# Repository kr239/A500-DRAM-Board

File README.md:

# A500-DRAM-Board

Replace the old 44256 DRAM chips on your A500+ with newer SOJ-40 EDO memory! No more hunting around trying to find stocks of old 44256 DRAM chips on eBay from dubious sellers with no idea if they work or not - i designed this board to fit 2 x 512KB (4MBit) EDO RAM chips so that you can address 1MB of RAM.

I used IS41C16257-35 chips (256k x 16) as they're cheap, abundant and they have exactly 9 address lines (A0 to A8) so no need for a CPLD to generate the A9 signal that's required for newer chips.

It's a pretty simple design, just three decoupling caps for each DRAM IC and the correct pin layout for it to plug into the A500 board. 

This Rev3 design reduces the component count, the board size and improves the layout and routing considerably.

Project is all done in KiCad 5.1.2

If you've been linked to this project from elsewhere - please note, while I might occasionally have some of these PCB's available, I don't typically have these produced and for sale, except for testing. To purchase one, please go here:

https://www.pcbway.com/project/shareproject/Amiga_500__DRAM_Replacement_Board.html

# Bill of Materials

6 x X7R 0.1uF MLCC SMD Capacitors (1206 (imperial))

2 x IS41C16257-35 5v 256x16 EDO DRAM (SOJ-40)

4 x 10-pin SIL Headers (Harwin M20-9771042)

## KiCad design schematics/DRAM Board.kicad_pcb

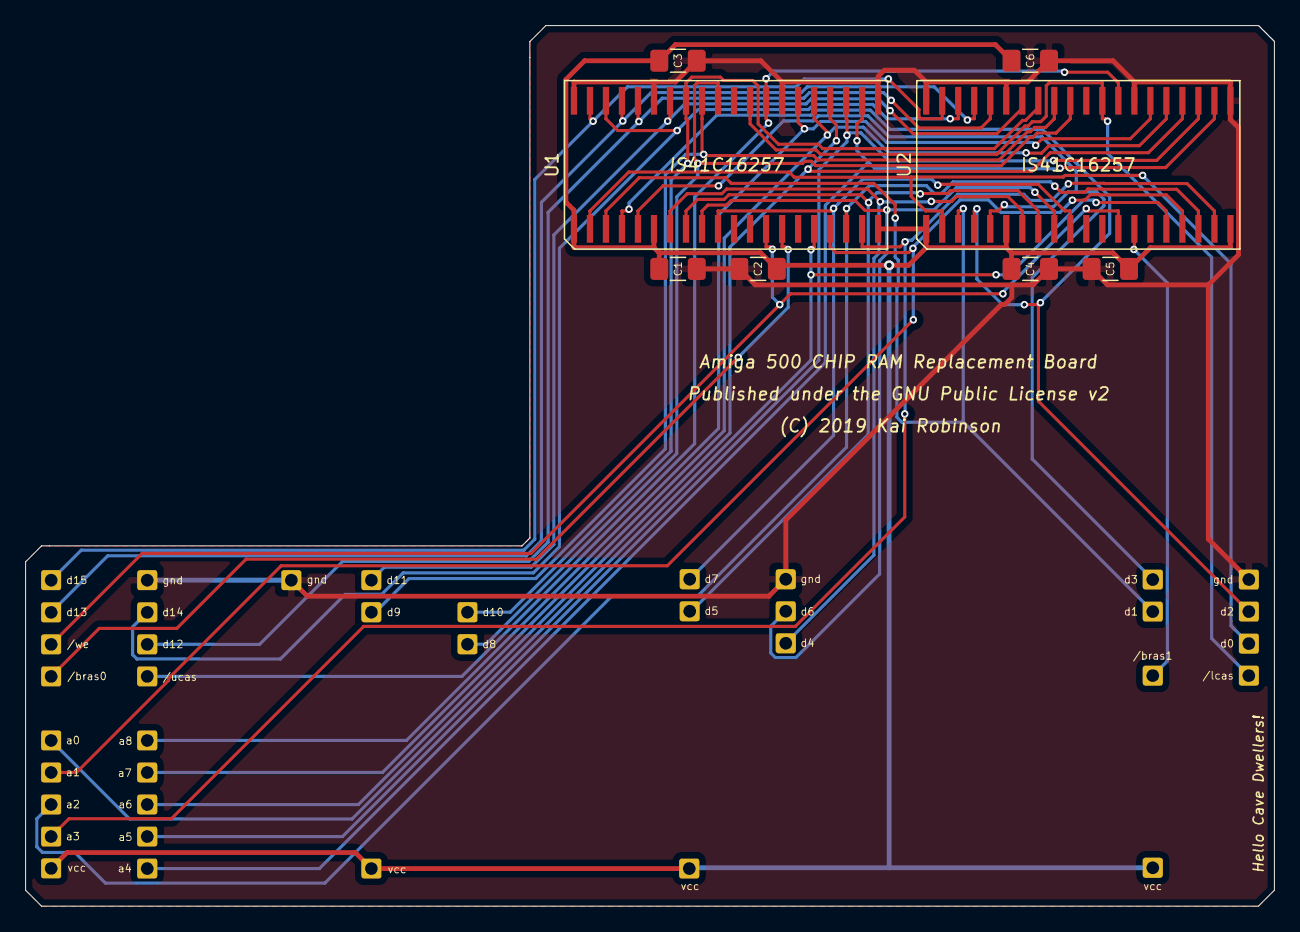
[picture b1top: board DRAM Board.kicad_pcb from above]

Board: 2 copper layers, 99.1 x 69.8 mm, 46 parts (0 on the bottom side), 32 nets.

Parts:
/bras0, /bras1: Conn_01x01; PinHeader_1x01_P2.54mm_Vertical
/lcas: Conn_01x01; PinHeader_1x01_P2.54mm_Vertical
/ucas: Conn_01x01; PinHeader_1x01_P2.54mm_Vertical
/we: Conn_01x01; PinHeader_1x01_P2.54mm_Vertical
C1, C2, C3, C4, C5, C6: 0.1uF; C_1206_3216Metric_Pad1.42x1.75mm_HandSolder
U1, U2: IS41C16257; SOJ-40
a0, a1, a2, a3, a4, a5, a6, a7, a8: Conn_01x01; PinHeader_1x01_P2.54mm_Vertical
d0, d1, d2, d3, d4, d5, d6, d7, d8, d9, d10, d11, d12, d13, d14, d15: Conn_01x01; PinHeader_1x01_P2.54mm_Vertical
gnd: Conn_01x01; PinHeader_1x01_P2.54mm_Vertical
gnd_u19, gnd_u20, gnd_u23: Conn_01x01; PinHeader_1x01_P2.54mm_Vertical
vcc_u17, vcc_u19, vcc_u20, vcc_u23: Conn_01x01; PinHeader_1x01_P2.54mm_Vertical

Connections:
/_bras0: /bras0.1, U1.14
/_bras1: /bras1.1, U2.14
/_lcas: /lcas.1, U1.29, U2.29
/_ucas: /ucas.1, U1.28, U2.28
/_we: /we.1, U1.13, U2.13
/a0: U1.16, U2.16, a0.1
/a1: U1.17, U2.17, a1.1
/a2: U1.18, U2.18, a2.1
/a3: U1.19, U2.19, a3.1
/a4: U1.22, U2.22, a4.1
/a5: U1.23, U2.23, a5.1
/a6: U1.24, U2.24, a6.1
/a7: U1.25, U2.25, a7.1
/a8: U1.26, U2.26, a8.1
/d0: U1.2, U2.2, d0.1
/d1: U1.3, U2.3, d1.1
/d2: U1.4, U2.4, d2.1
/d3: U1.5, U2.5, d3.1
/d4: U1.7, U2.7, d4.1
/d5: U1.8, U2.8, d5.1
/d6: U1.9, U2.9, d6.1
/d7: U1.10, U2.10, d7.1
/d8: U1.31, U2.31, d8.1
/d9: U1.32, U2.32, d9.1
/d10: U1.33, U2.33, d10.1
/d11: U1.34, U2.34, d11.1
/d12: U1.36, U2.36, d12.1
/d13: U1.37, U2.37, d13.1
/d14: U1.38, U2.38, d14.1
/d15: U1.39, U2.39, d15.1
/gnd: C1.2, C2.2, C3.2, C4.2, C5.2, C6.2, U1.21, U1.27, U1.35, U1.40, U2.21, U2.27, U2.35, U2.40, gnd.1, gnd_u19.1, gnd_u20.1, gnd_u23.1
/vcc5: C1.1, C2.1, C3.1, C4.1, C5.1, C6.1, U1.1, U1.6, U1.20, U2.1, U2.6, U2.20, vcc_u17.1, vcc_u19.1, vcc_u20.1, vcc_u23.1

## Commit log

2019-10-02 Add files via upload
    Update Gerbers - v3.0, moves the SOJ's inward to stop fouling on the case.

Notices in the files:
schematics/DRAM Board.kicad_pcb:
(C) 2019 Kai Robinson
Published under the GNU Public License v2
